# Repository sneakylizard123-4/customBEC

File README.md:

# customBEC
A custom made battery elimination circuit.
output 5V 3A 15W.
30x30 size for 5" drones and other projects that need 5v supply

## How to use
there is a +batt and -batt, connect battery there
there is +5V and GND for output

# Pictures

blender render:

PCB:

schematic:

# Prices

# LCSC

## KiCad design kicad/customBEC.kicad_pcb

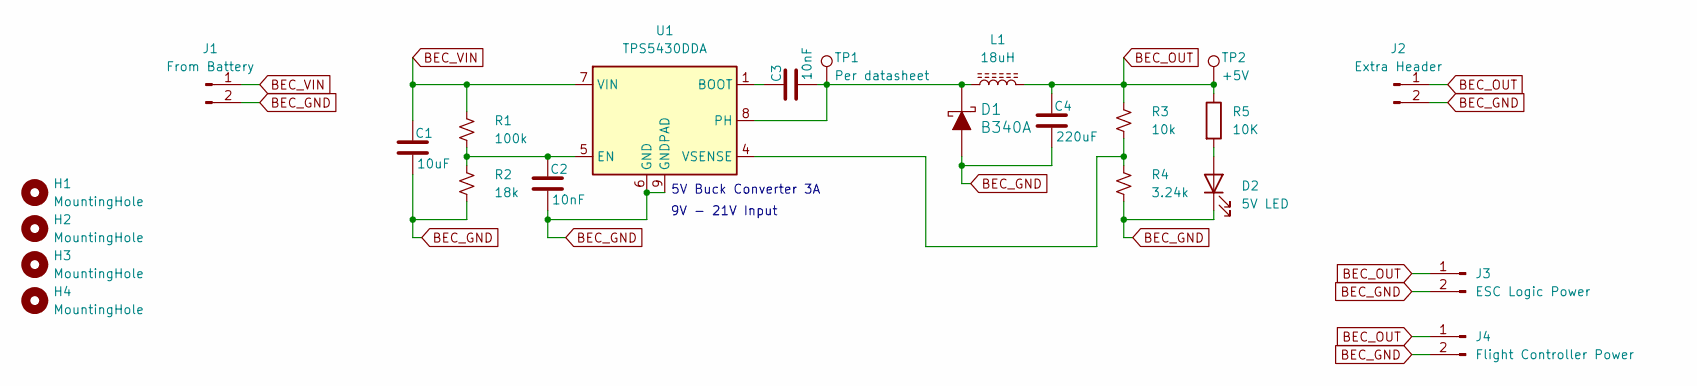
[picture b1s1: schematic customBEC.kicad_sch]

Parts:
C1: 10uF; C_1206_3216Metric_Pad1.33x1.80mm_HandSolder
C2, C3: 10nF; C_0603_1608Metric_Pad1.08x0.95mm_HandSolder
C4: 220uF; C_1206_3216Metric_Pad1.33x1.80mm_HandSolder
D1: B340A; DO-214AC; MPN B340A-13-F; Digi-Key_PN B340A-FDICT-ND
D2: 5V LED; LED_0805_2012Metric_Pad1.15x1.40mm_HandSolder
H1, H2, H3, H4: MountingHole; MountingHole_3.2mm_M3
J1: From Battery; Hirose_DF13-02P-1.25DS_1x02_P1.25mm_Horizontal
J2: Extra Header; PinHeader_1x02_P2.54mm_Vertical
J3: ESC Logic Power; Hirose_DF13-02P-1.25DS_1x02_P1.25mm_Horizontal
J4: Flight Controller Power; Hirose_DF13-02P-1.25DS_1x02_P1.25mm_Horizontal
L1: 18uH; L_Taiyo-Yuden_NR-50xx_HandSoldering
R1: 100k; R_0805_2012Metric_Pad1.20x1.40mm_HandSolder
R2: 18k; R_0805_2012Metric_Pad1.20x1.40mm_HandSolder
R3: 10k; R_0603_1608Metric_Pad0.98x0.95mm_HandSolder
R4: 3.24k; R_0603_1608Metric_Pad0.98x0.95mm_HandSolder
R5: 10K; R_0603_1608Metric_Pad0.98x0.95mm_HandSolder
TP1: Per datasheet; TestPoint_Pad_1.0x1.0mm
TP2: +5V; TestPoint_Pad_1.0x1.0mm
U1: TPS5430DDA; TI_SO-PowerPAD-8_ThermalVias

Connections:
BEC_GND: C1.2, C2.2, C4.2, D1.A, D2.1 (K), J1.2, J2.2, J3.2, J4.2, R2.2, R4.2, U1.6 (GND), U1.9 (GNDPAD)
BEC_OUT: C4.1, J2.1, J3.1, J4.1, L1.2, R3.1, R5.1, TP2.1
BEC_VIN: C1.1, J1.1, R1.1, U1.7 (VIN)
unnamed: D2.2 (A), R5.2
unnamed: C3.1, U1.1 (BOOT)
unnamed: C2.1, R1.2, R2.1, U1.5 (EN)
unnamed: C3.2, D1.K, L1.1, TP1.1, U1.8 (PH)
unnamed: R3.2, R4.1, U1.4 (VSENSE)

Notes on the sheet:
9V - 21V Input
5V Buck Converter 3A

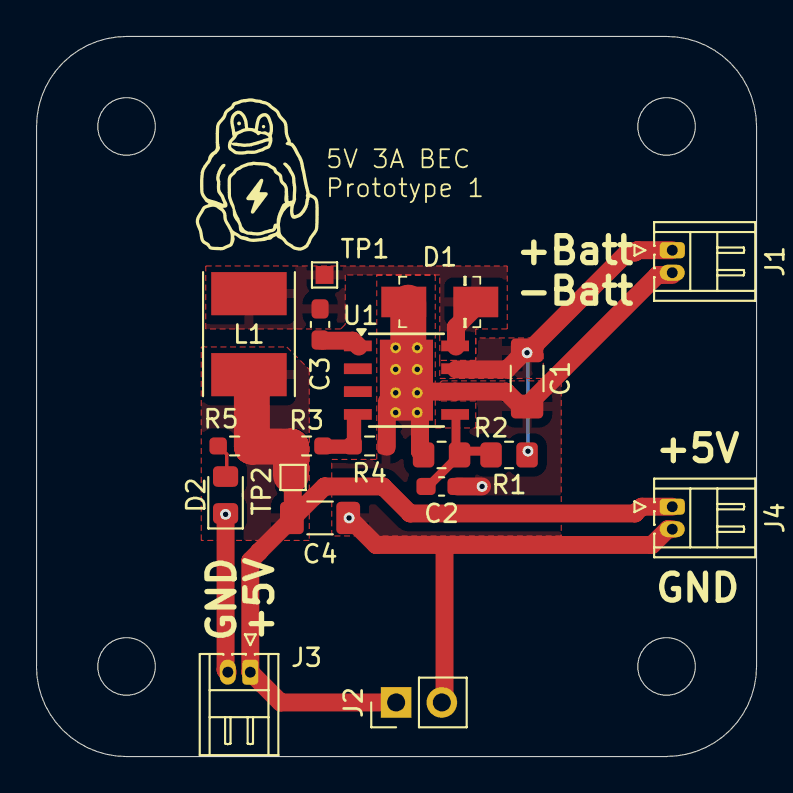
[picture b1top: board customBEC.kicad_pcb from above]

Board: 2 copper layers, 40.0 x 40.0 mm, 23 parts (0 on the bottom side), 8 nets.

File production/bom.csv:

Designator,Footprint,Quantity,Value,LCSC Part #
C1,1206,1,10uF,
"C2, C3",0603,2,10nF,
C4,1206,1,220uF,
D1,DO-214AC,1,B340A,B340A-13-F
D2,0805,1,5V LED,
J1,Hirose_DF13-02P-1.25DS_1x02_P1.25mm_Horizontal,1,From Battery,
J2,PinHeader_1x02_P2.54mm_Vertical,1,Extra Header,
J3,Hirose_DF13-02P-1.25DS_1x02_P1.25mm_Horizontal,1,ESC Logic Power,
J4,Hirose_DF13-02P-1.25DS_1x02_P1.25mm_Horizontal,1,Flight Controller Power,
L1,L_Taiyo-Yuden_NR-50xx_HandSoldering,1,18uH,
R1,0805,1,100k,
R2,0805,1,18k,
"R3, R5",0603,2,10k,
R4,0603,1,3.24k,
TP1,TestPoint_Pad_1.0x1.0mm,1,Per datasheet,
TP2,TestPoint_Pad_1.0x1.0mm,1,+5V,
U1,TI_SO-PowerPAD-8_ThermalVias,1,TPS5430DDA,

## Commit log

2026-01-27 kicad parts
2026-01-27 Made Board Traces Cleaner
2026-01-27 Made Traces thicker for more power capabilities. i dunno if the vias can handle though
2026-01-27 re-annotate and fix drc issues
2026-01-27 rebuild gerber files
2026-01-27 remove unnecessary silkscreen
2026-01-27 rebuild board gerber
2026-01-27 add picture
2026-01-27 rebuild gerbers and add blender file
2026-01-27 Add project description for customBEC
2026-01-27 Update README with usage instructions
    Added usage instructions for the customBEC.
2026-01-27 Update README.md with images and formatting
    Added images for the blender render and schematic.
2026-02-16 move kicad files into kicad folder
2026-02-16 add images and using handsoldering
2026-02-16 random things
